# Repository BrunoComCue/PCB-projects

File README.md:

# PCB-projects

Examples of PCB designs made from scratch in order to learn and practice

KiCAD, EAGLE, Altium Designer

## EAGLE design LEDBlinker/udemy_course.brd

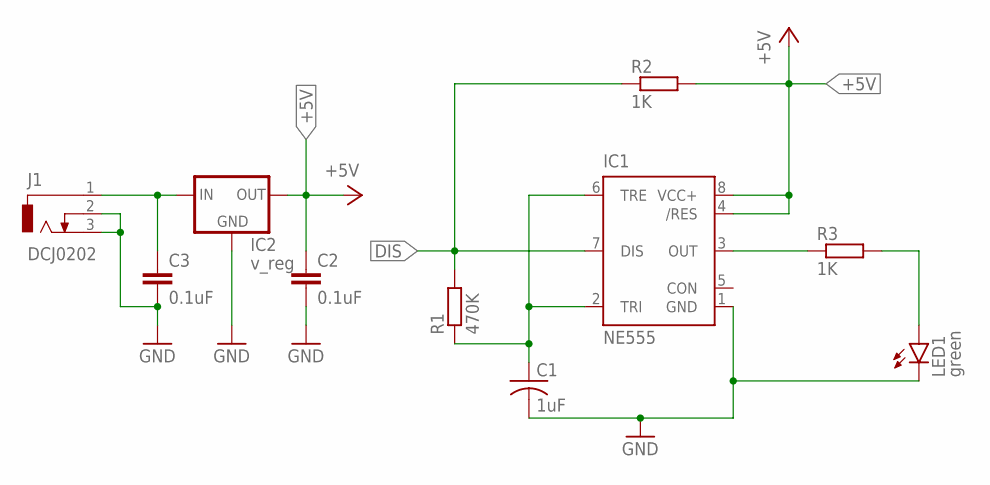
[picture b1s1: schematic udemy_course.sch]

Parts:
C1: 1uF; C050-045X075
C2, C3: 0.1uF; C025-050X050
IC1: NE555; DIL-08
IC2: v_reg; 78XXS
J1: DCJ0202
LED1: green; LED5MM
R1: 470K; 0411/15
R2, R3: 1K; 0411/15

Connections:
+5V: C2.1, IC1.4 (/RES), IC1.8 (VCC+), IC2.OUT, R2.2
DIS: IC1.7 (DIS), R1.2, R2.1
GND: C1.2, C2.2, C3.2, IC1.1 (GND), IC2.GND, J1.2, J1.3, LED1.K (C)
unnamed: C3.1, IC2.IN, J1.1
unnamed: IC1.3 (OUT), R3.1
unnamed: LED1.A, R3.2
unnamed: C1.1, IC1.2 (TRI), IC1.6 (TRE), R1.1

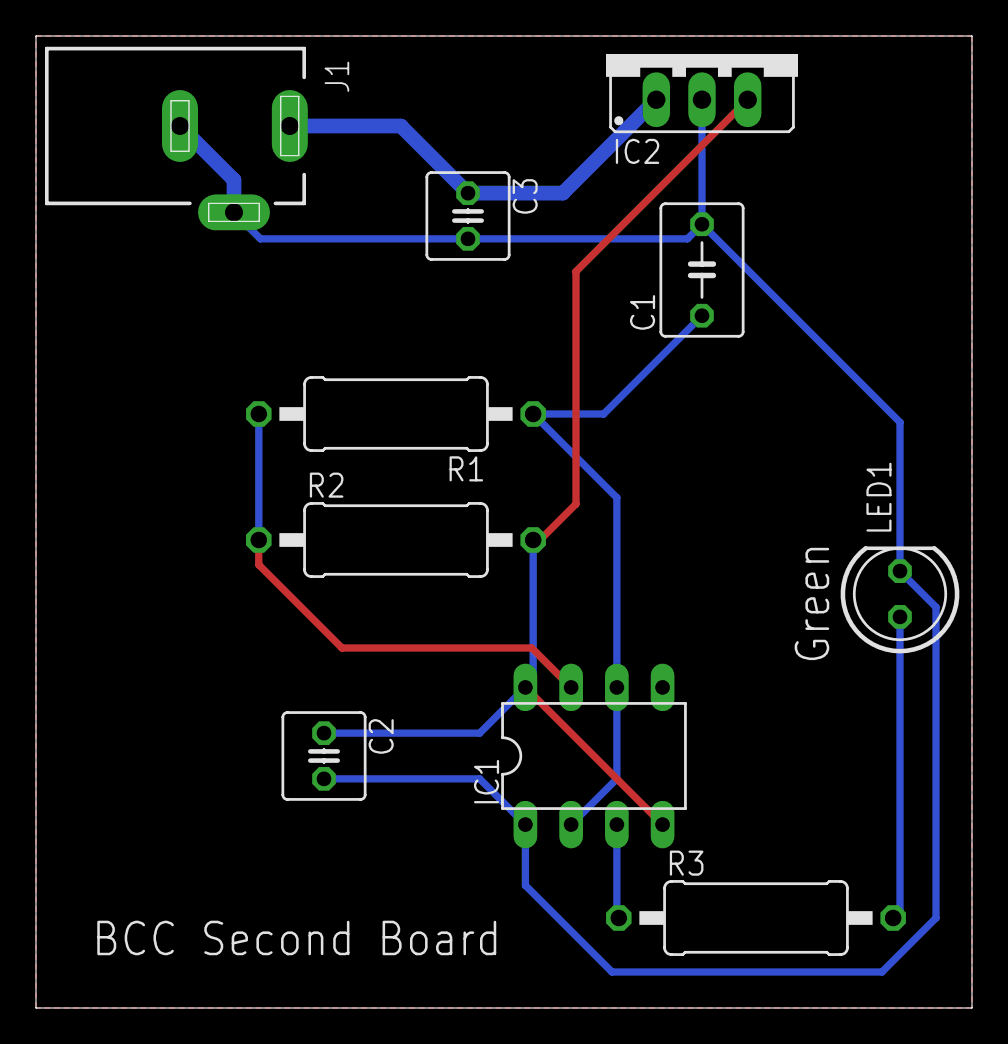
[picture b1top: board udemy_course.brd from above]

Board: 2 copper layers, 52.0 x 54.0 mm, 10 parts (0 on the bottom side), 7 nets.

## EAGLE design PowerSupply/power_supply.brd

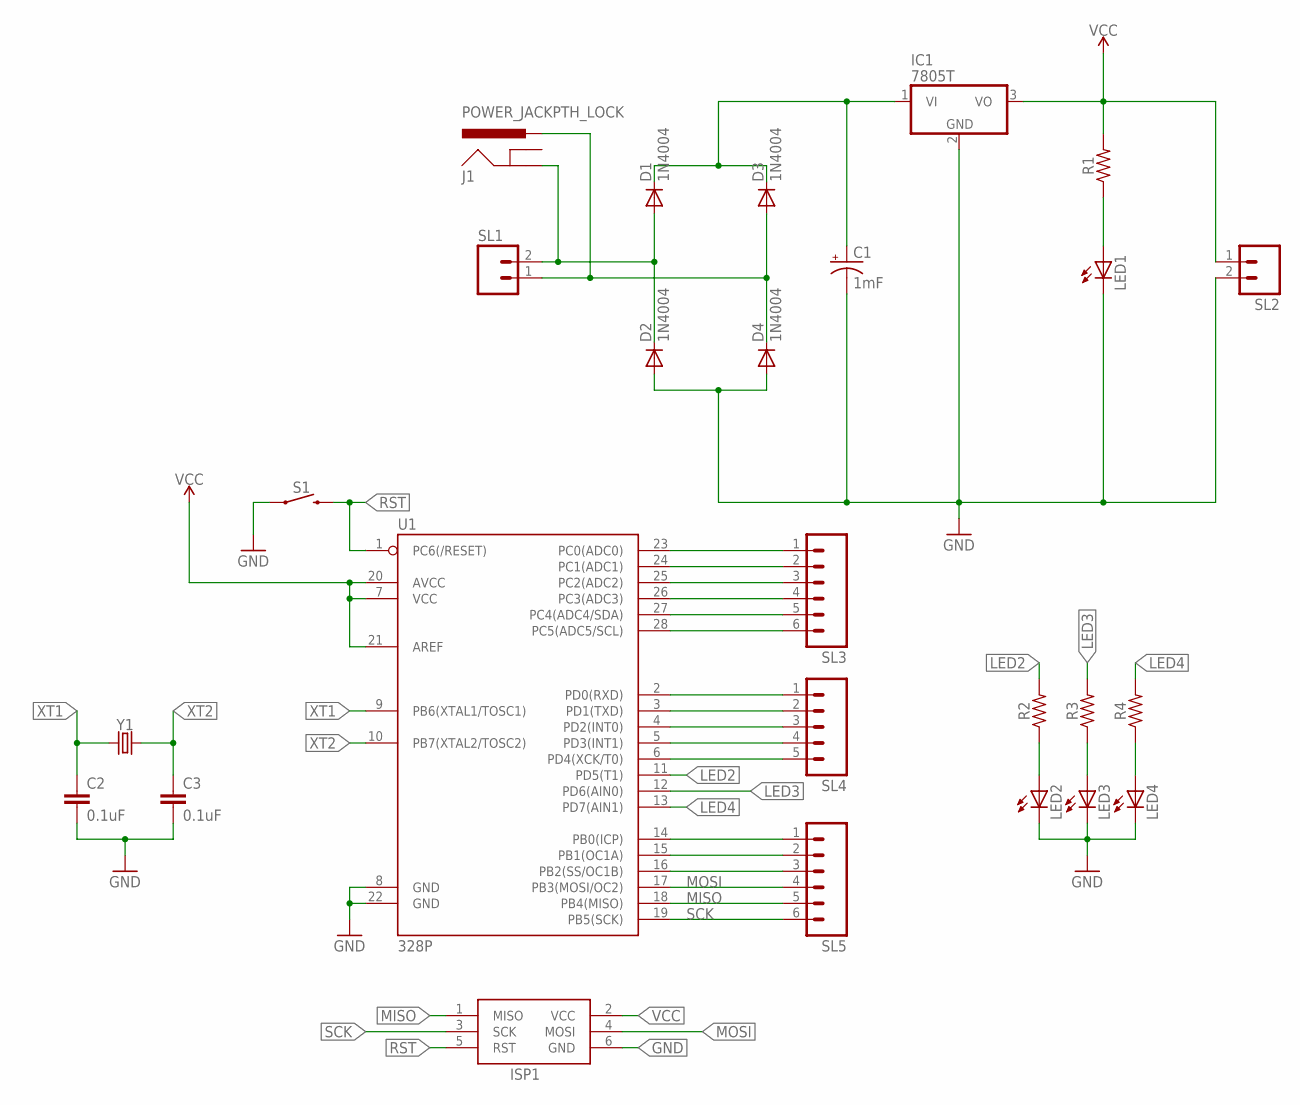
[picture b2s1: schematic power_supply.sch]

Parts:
C1: 1mF; CPOL-RADIAL-5MM-10MM
C2, C3: 0.1uF; CAP-PTH-SMALL-KIT
D1, D2, D3, D4: 1N4004; DO41-10
IC1: 7805T; TO220H
ISP1: AVRISP-6; AVRISP
J1: POWER_JACKPTH_LOCK; POWER_JACK_PTH_LOCK
LED1: LED5MM
LED2, LED3, LED4: LED3MM
R1, R2, R3, R4: AXIAL-0.3
S1: MOMENTARY-SWITCH-SPST-PTH-6.0MM; TACTILE_SWITCH_PTH_6.0MM
SL1, SL2: M02; 02P
SL3, SL5: M06; 06P
SL4: M05; 05P
U1: 328P; DIP28
Y1: CRYSTALPTH-HC49US; HC49US

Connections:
GND: C1.-, C2.2, C3.2, D2.A, D4.A, IC1.2 (GND), ISP1.6 (GND), LED1.K (C), LED2.K (C), LED3.K (C), LED4.K (C), S1.1, SL2.2, U1.8 (GND), U1.22 (GND)
LED2: R2.P$2 (2), U1.11 (PD5(T1))
LED3: R3.P$2 (2), U1.12 (PD6(AIN0))
LED4: R4.P$2 (2), U1.13 (PD7(AIN1))
MISO: ISP1.1 (MISO), SL5.5, U1.18 (PB4(MISO))
MOSI: ISP1.4 (MOSI), SL5.4, U1.17 (PB3(MOSI/OC2))
unnamed: D1.A, D2.C, J1.GND, SL1.2
unnamed: D3.A, D4.C, J1.PWR, SL1.1
unnamed: C1.+, D1.C, D3.C, IC1.1 (VI)
unnamed: SL3.1, U1.23 (PC0(ADC0))
unnamed: LED1.A, R1.P$1 (1)
unnamed: LED2.A, R2.P$1 (1)
unnamed: LED3.A, R3.P$1 (1)
unnamed: LED4.A, R4.P$1 (1)
unnamed: SL3.2, U1.24 (PC1(ADC1))
unnamed: SL3.3, U1.25 (PC2(ADC2))
unnamed: SL3.4, U1.26 (PC3(ADC3))
unnamed: SL3.5, U1.27 (PC4(ADC4/SDA))
unnamed: SL3.6, U1.28 (PC5(ADC5/SCL))
unnamed: SL4.5, U1.6 (PD4(XCK/T0))
unnamed: SL4.4, U1.5 (PD3(INT1))
unnamed: SL4.3, U1.4 (PD2(INT0))
unnamed: SL4.2, U1.3 (PD1(TXD))
unnamed: SL4.1, U1.2 (PD0(RXD))
unnamed: SL5.1, U1.14 (PB0(ICP))
unnamed: SL5.2, U1.15 (PB1(OC1A))
unnamed: SL5.3, U1.16 (PB2(SS/OC1B))
RST: ISP1.5 (RST), S1.3 (2), U1.1 (PC6(/RESET))
SCK: ISP1.3 (SCK), SL5.6, U1.19 (PB5(SCK))
VCC: IC1.3 (VO), ISP1.2 (VCC), R1.P$2 (2), SL2.1, U1.7 (VCC), U1.20 (AVCC), U1.21 (AREF)
XT1: C2.1, U1.9 (PB6(XTAL1/TOSC1)), Y1.1
XT2: C3.1, U1.10 (PB7(XTAL2/TOSC2)), Y1.2

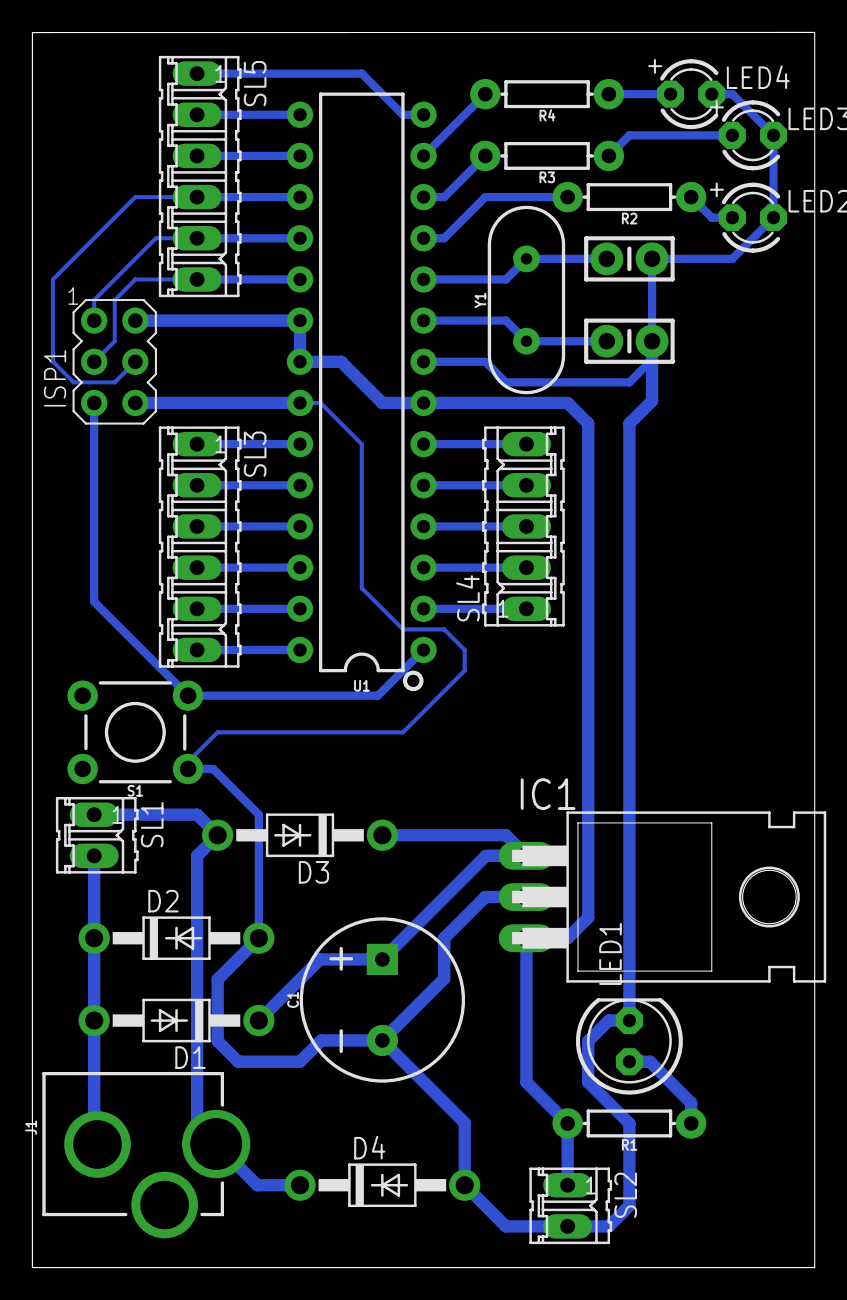
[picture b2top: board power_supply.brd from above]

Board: 2 copper layers, 48.3 x 76.2 mm, 26 parts (0 on the bottom side), 32 nets.

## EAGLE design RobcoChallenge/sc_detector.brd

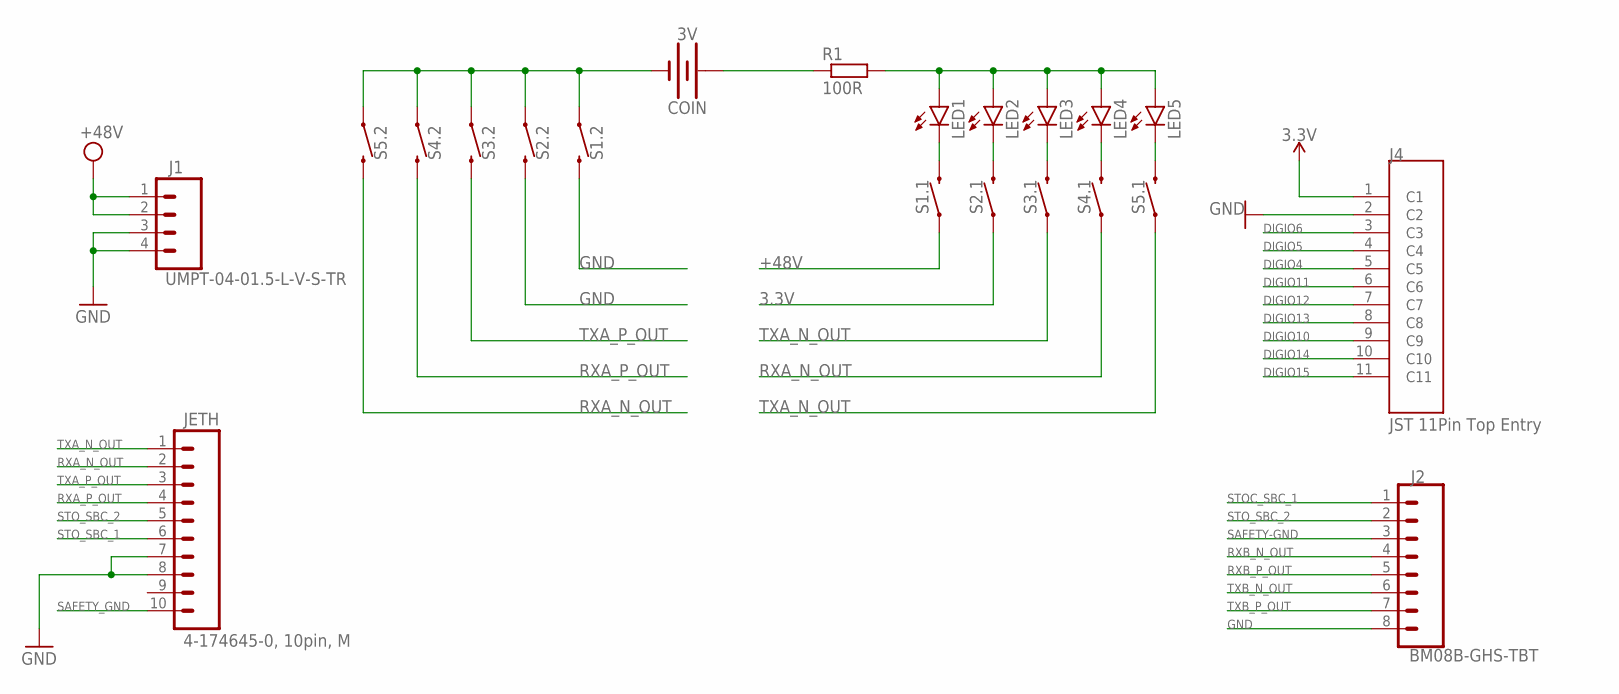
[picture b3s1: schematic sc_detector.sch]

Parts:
COIN: 3V; BATTCON_12MM
J1: UMPT-04-01.5-L-V-S-TR; JST-4-SMD
J2: BM08B-GHS-TBT; 1X08_SMD_MALE
J4: JST 11Pin Top Entry; ROBCO_CONN
JETH: 4-174645-0, 10pin, M; 1X10_SMD_MALE
LED1, LED2, LED3, LED4, LED5: LEDCHIP-LED0805; CHIP-LED0805
R1: 100R; R0805
S1.1, S1.2, S2.1, S2.2, S3.1, S3.2, S4.1, S4.2, S5.1, S5.2: MOMENTARY-SWITCH-SPST-SMD-6.0X3.5MM; TACTILE_SWITCH_SMD_6.0X3.5MM

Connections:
3.3V: J4.1 (C1), S2.1.1
+48V: J1.1, J1.2, S1.1.1
DIGIO4: J4.5 (C5)
DIGIO5: J4.4 (C4)
DIGIO6: J4.3 (C3)
DIGIO10: J4.9 (C9)
DIGIO11: J4.6 (C6)
DIGIO12: J4.7 (C7)
DIGIO13: J4.8 (C8)
DIGIO14: J4.10 (C10)
DIGIO15: J4.11 (C11)
GND: J1.3, J1.4, J2.8, J4.2 (C2), JETH.7, JETH.8, S1.2.2, S2.2.2
IN: LED1.A, LED2.A, LED3.A, LED4.A, LED5.A, R1.2
unnamed: LED5.C, S5.1.2
unnamed: LED3.C, S3.1.2
unnamed: LED1.C, S1.1.2
unnamed: LED2.C, S2.1.2
unnamed: LED4.C, S4.1.2
unnamed: COIN.PWR@1 (+), R1.1
NEG: COIN.GND (-), S1.2.1, S2.2.1, S3.2.1, S4.2.1, S5.2.1
RXA_N_OUT: JETH.2, S4.1.1, S5.2.2
RXA_P_OUT: JETH.4, S4.2.2
RXB_N_OUT: J2.4
RXB_P_OUT: J2.5
SAFETY-GND: J2.3
SAFETY_GND: JETH.10
STOC_SBC_1: J2.1
STO_SBC_1: JETH.6
STO_SBC_2: J2.2, JETH.5
TXA_N_OUT: JETH.1, S3.1.1, S5.1.1
TXA_P_OUT: JETH.3, S3.2.2
TXB_N_OUT: J2.6
TXB_P_OUT: J2.7

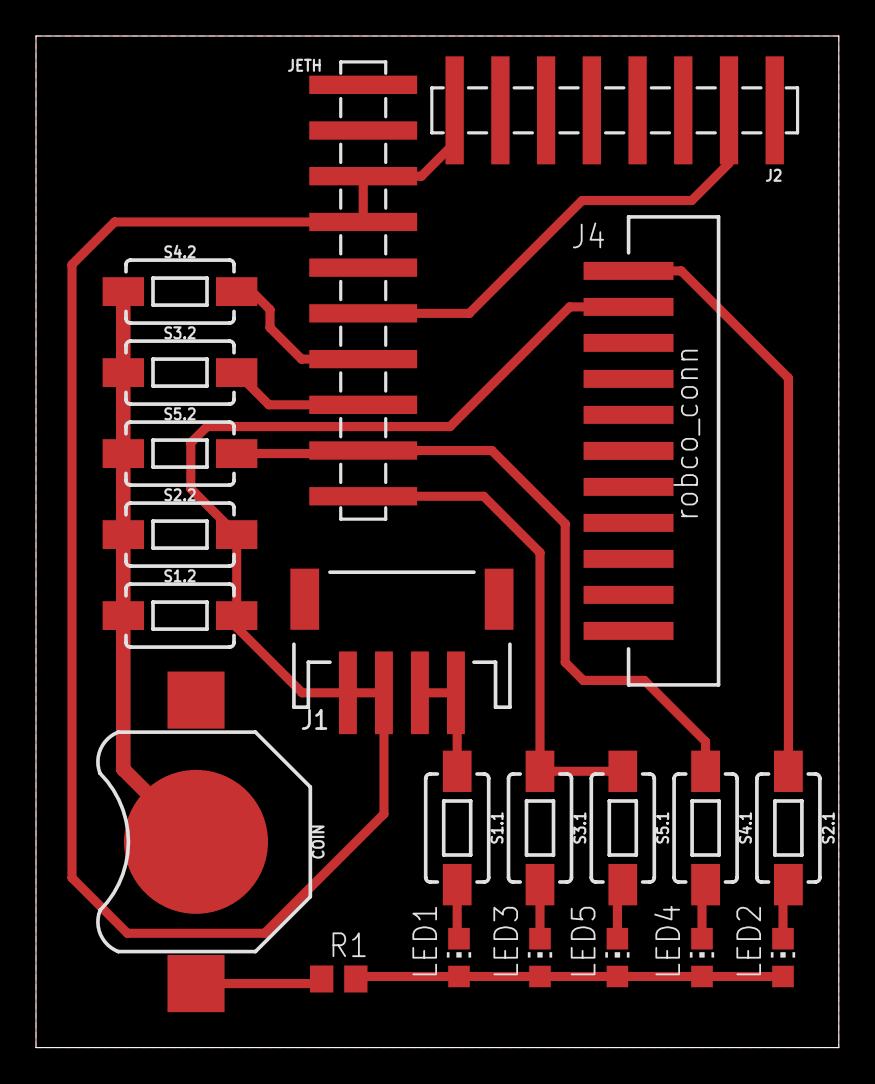
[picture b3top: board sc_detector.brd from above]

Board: 2 copper layers, 44.6 x 56.2 mm, 21 parts (0 on the bottom side), 16 nets.

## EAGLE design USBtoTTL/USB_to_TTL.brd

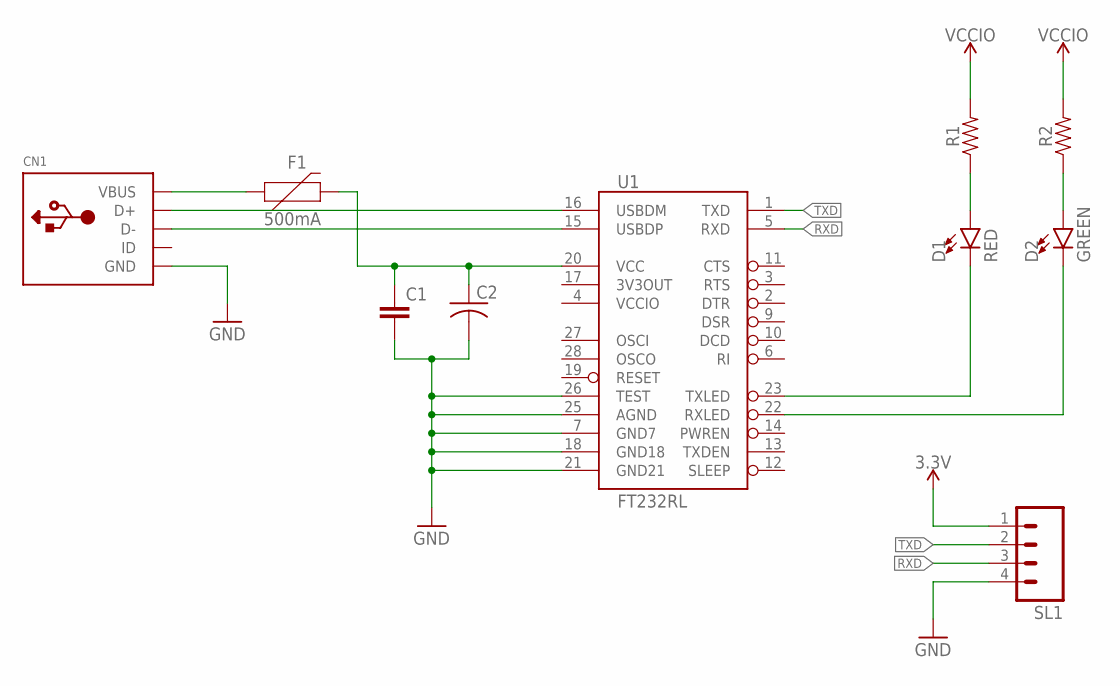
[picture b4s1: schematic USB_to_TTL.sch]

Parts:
C1: C-EUC1206; C1206
C2: C-USC1206; C1206
CN1: USBMINIB; USB-MINIB
D1: RED; LED-1206
D2: GREEN; LED-1206
F1: 500mA; 1206
R1, R2: 1206
SL1: M04; 04P
U1: FT232RL; SSOP28DB

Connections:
3.3V: SL1.1
GND: C1.2, C2.2, CN1.GND, SL1.4, U1.7 (GND7), U1.18 (GND18), U1.21 (GND21), U1.25 (AGND), U1.26 (TEST)
unnamed: CN1.VBUS, F1.1
unnamed: C1.1, C2.1, F1.2, U1.20 (VCC)
unnamed: CN1.D+, U1.16 (USBDM)
unnamed: CN1.D-, U1.15 (USBDP)
unnamed: D1.C, U1.23 (TXLED)
unnamed: D2.C, U1.22 (RXLED)
unnamed: D1.A, R1.1
unnamed: D2.A, R2.1
RXD: SL1.3, U1.5 (RXD)
TXD: SL1.2, U1.1 (TXD)
VCCIO: R1.2, R2.2, U1.4 (VCCIO)

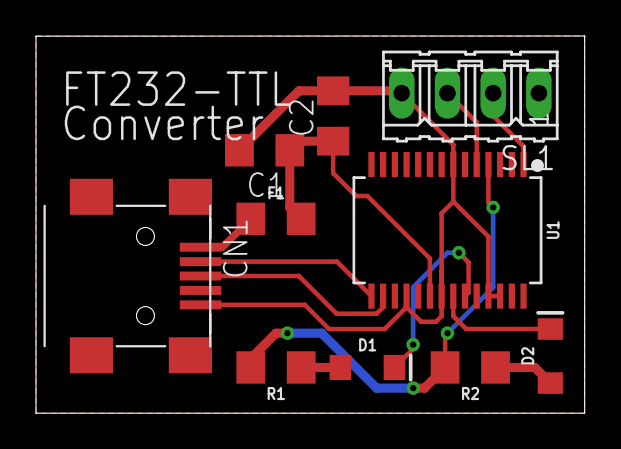
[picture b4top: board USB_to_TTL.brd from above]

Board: 2 copper layers, 30.5 x 21.0 mm, 10 parts (0 on the bottom side), 12 nets.

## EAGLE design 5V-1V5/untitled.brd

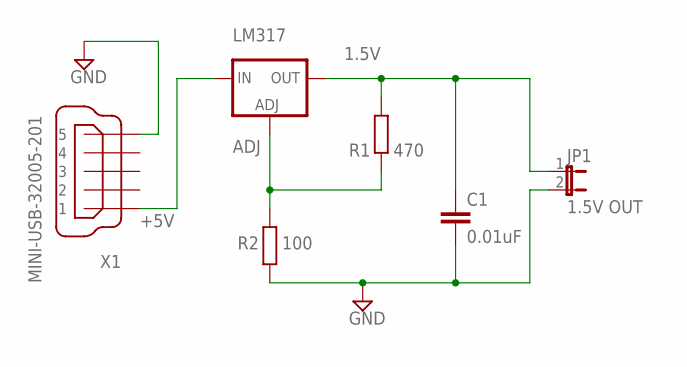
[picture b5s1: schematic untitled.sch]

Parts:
C1: 0.01uF; C050-025X075
JP1: 1.5V OUT; JP1
LM317: LM317TL; 317TL
R1: 470; 0204/7
R2: 100; 0204/7
X1: MINI-USB-32005-201; 32005-201

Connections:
1.5V: C1.1, JP1.1, LM317.2 (OUT), R1.2
+5V: LM317.3 (IN), X1.1
ADJ: LM317.1 (ADJ), R1.1, R2.2
GND: C1.2, JP1.2, R2.1, X1.5

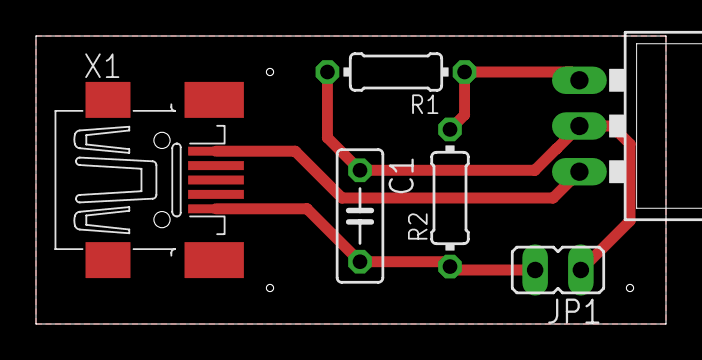
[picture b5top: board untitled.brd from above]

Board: 2 copper layers, 35.0 x 16.0 mm, 6 parts (0 on the bottom side), 4 nets.

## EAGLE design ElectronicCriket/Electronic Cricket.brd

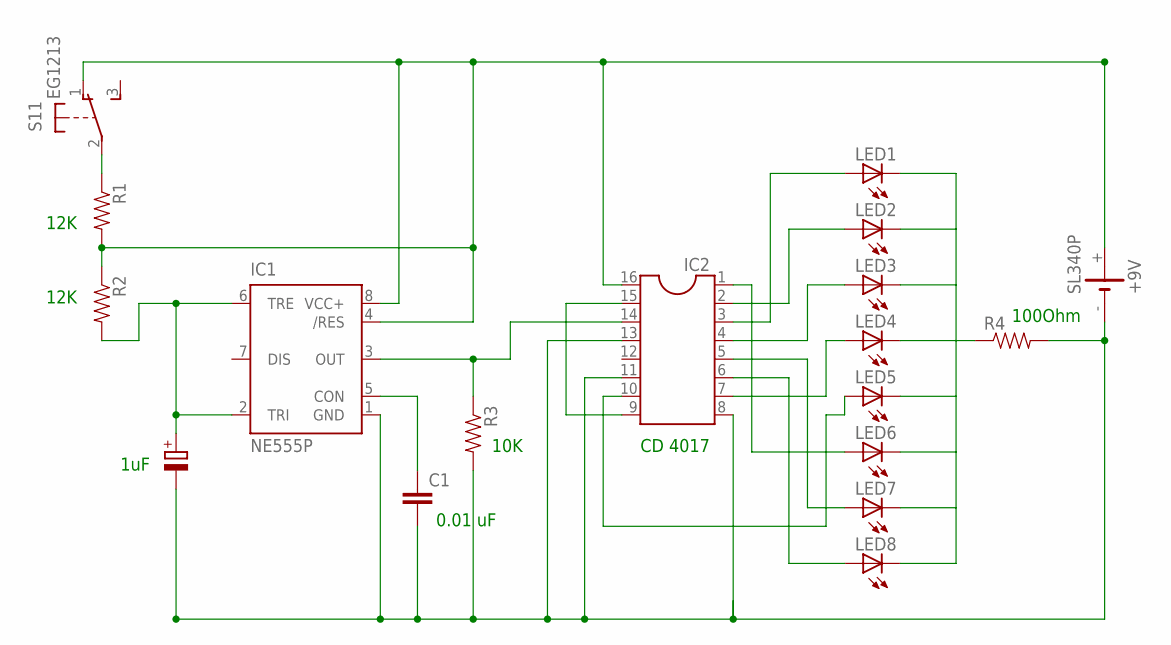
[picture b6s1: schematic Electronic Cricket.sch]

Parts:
+9V: SL340P; SL-340/P3.6V
C1: C2.5/6; C2.5-6
IC1: NE555P; DIL-08
IC2: DIL16
LED1, LED2, LED3, LED4, LED5, LED6, LED7, LED8: LEDB156; Q62902-B156
R1, R2, R3, R4: RESISTORAXIAL-0.3; AXIAL-0.3
S1: EG1213

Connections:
unnamed: IC2.3, LED1.A
unnamed: IC2.2, LED2.A
unnamed: IC2.4, LED3.A
unnamed: IC2.7, LED4.A
unnamed: IC2.10, LED5.A
unnamed: IC2.1, LED6.A
unnamed: IC2.5, LED7.A
unnamed: IC2.9, IC2.15
unnamed: +9V.-, C1.2, IC1.1 (GND), IC2.8, IC2.11, IC2.13, R3.P$2 (2), R4.P$2 (2)
unnamed: IC2.6, LED8.A
unnamed: R1.P$1 (1), S1.2
unnamed: LED1.K (C), LED2.K (C), LED3.K (C), LED4.K (C), LED5.K (C), LED6.K (C), LED7.K (C), LED8.K (C), R4.P$1 (1)
unnamed: IC1.3 (OUT), IC2.14, R3.P$1 (1)
unnamed: +9V.+, IC1.4 (/RES), IC1.8 (VCC+), IC2.16, R1.P$2 (2), R2.P$1 (1), S1.1 (O)
unnamed: IC1.2 (TRI), IC1.6 (TRE), R2.P$2 (2)
unnamed: C1.1, IC1.5 (CON)

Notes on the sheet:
12K
10K
100Ohm
1uF
0.01 uF
CD 4017

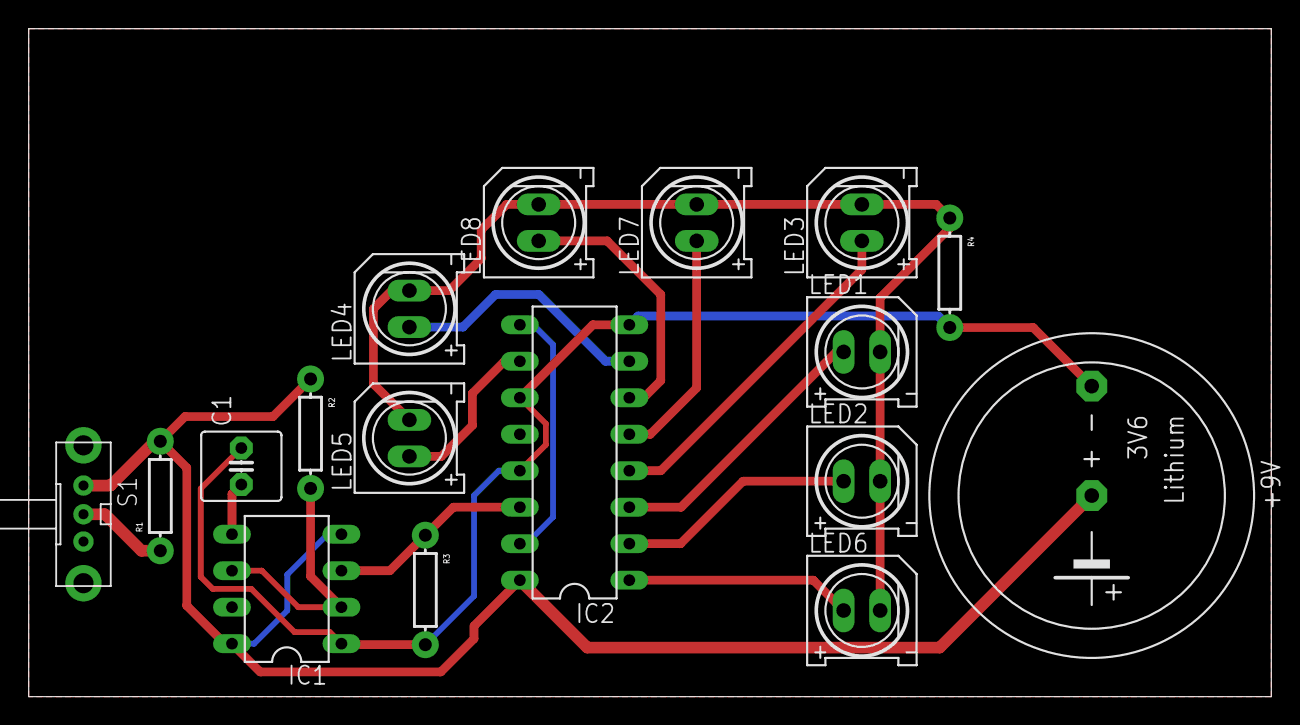
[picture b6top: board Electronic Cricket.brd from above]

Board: 2 copper layers, 86.5 x 46.5 mm, 17 parts (0 on the bottom side), 16 nets.

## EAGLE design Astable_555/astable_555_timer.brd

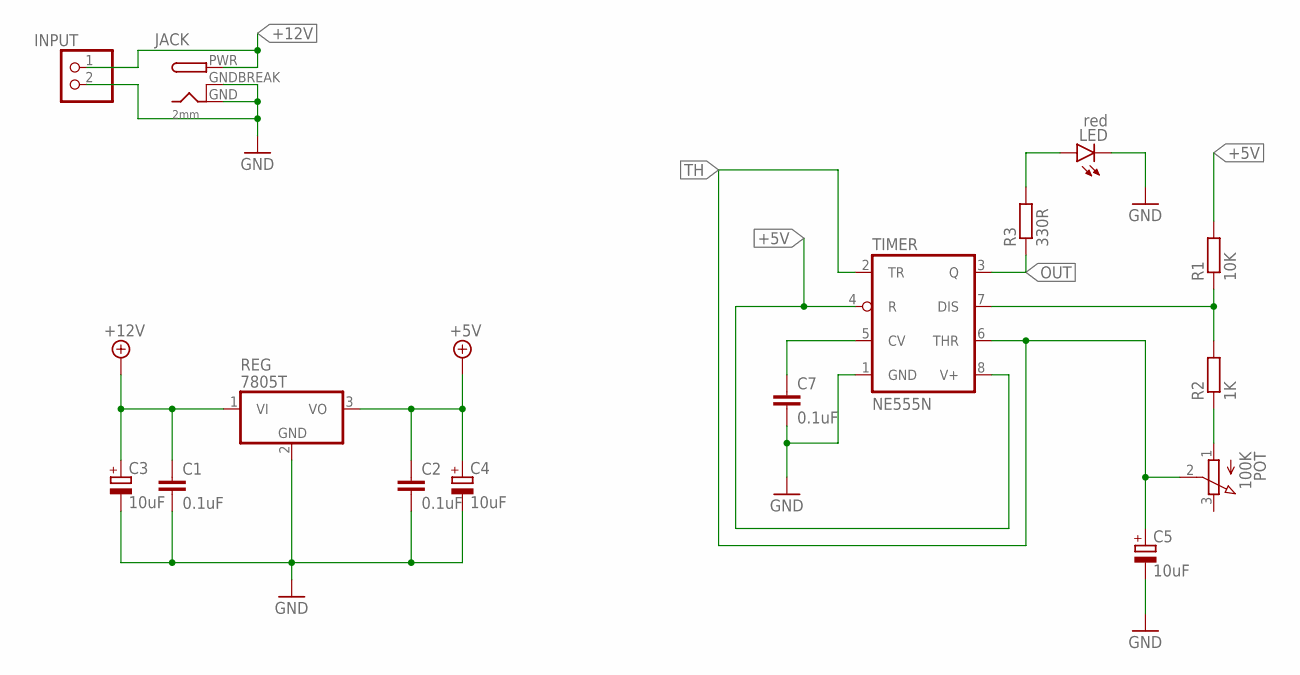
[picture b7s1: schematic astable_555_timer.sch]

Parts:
C1, C2, C7: 0.1uF; C050-030X075
C3, C4, C5: 10uF; E3,5-8
INPUT: PINHD-1X2; 1X02
JACK: 2mm; DCJACK_2MM_PTH
LED: red; LED5MM
POT: 100K; 3RP/1610N
R1: 10K; 0207/10
R2: 1K; 0207/10
R3: 330R; 0207/10
REG: 7805T; TO220H
TIMER: NE555N; DIL08

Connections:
+5V: C2.1, C4.+, R1.2, REG.3 (VO), TIMER.4 (R), TIMER.8 (V+)
+12V: C1.1, C3.+, INPUT.1, JACK.PWR, REG.1 (VI)
GND: C1.2, C2.2, C3.-, C4.-, C5.-, C7.2, INPUT.2, JACK.GND, JACK.GNDBREAK, LED.K (C), REG.2 (GND), TIMER.1 (GND)
unnamed: LED.A, R3.2
unnamed: R1.1, R2.2, TIMER.7 (DIS)
unnamed: POT.1 (A), R2.1
unnamed: C7.1, TIMER.5 (CV)
OUT: R3.1, TIMER.3 (Q)
TH: C5.+, POT.2 (S), TIMER.2 (TR), TIMER.6 (THR)

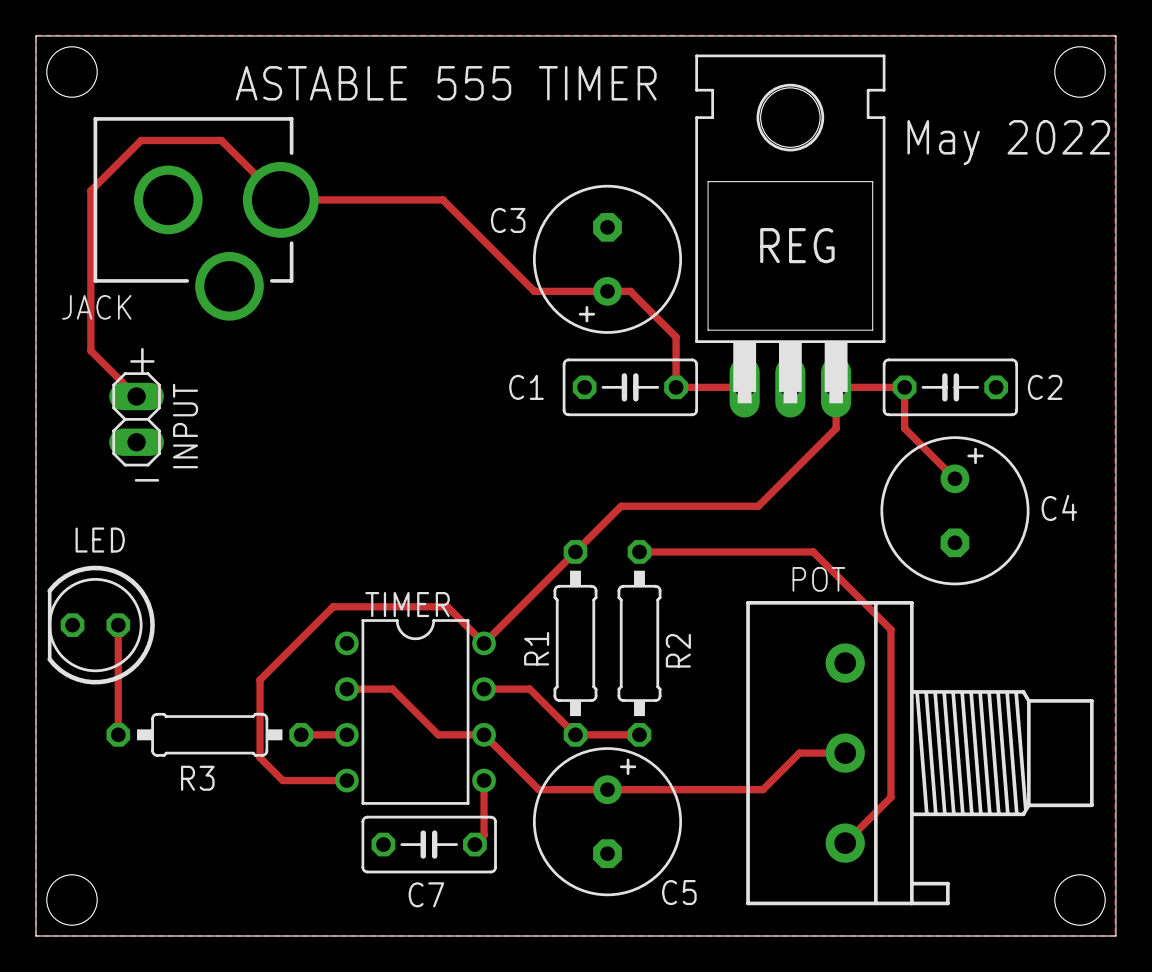
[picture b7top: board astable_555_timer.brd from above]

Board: 2 copper layers, 60.0 x 50.0 mm, 15 parts (0 on the bottom side), 9 nets.

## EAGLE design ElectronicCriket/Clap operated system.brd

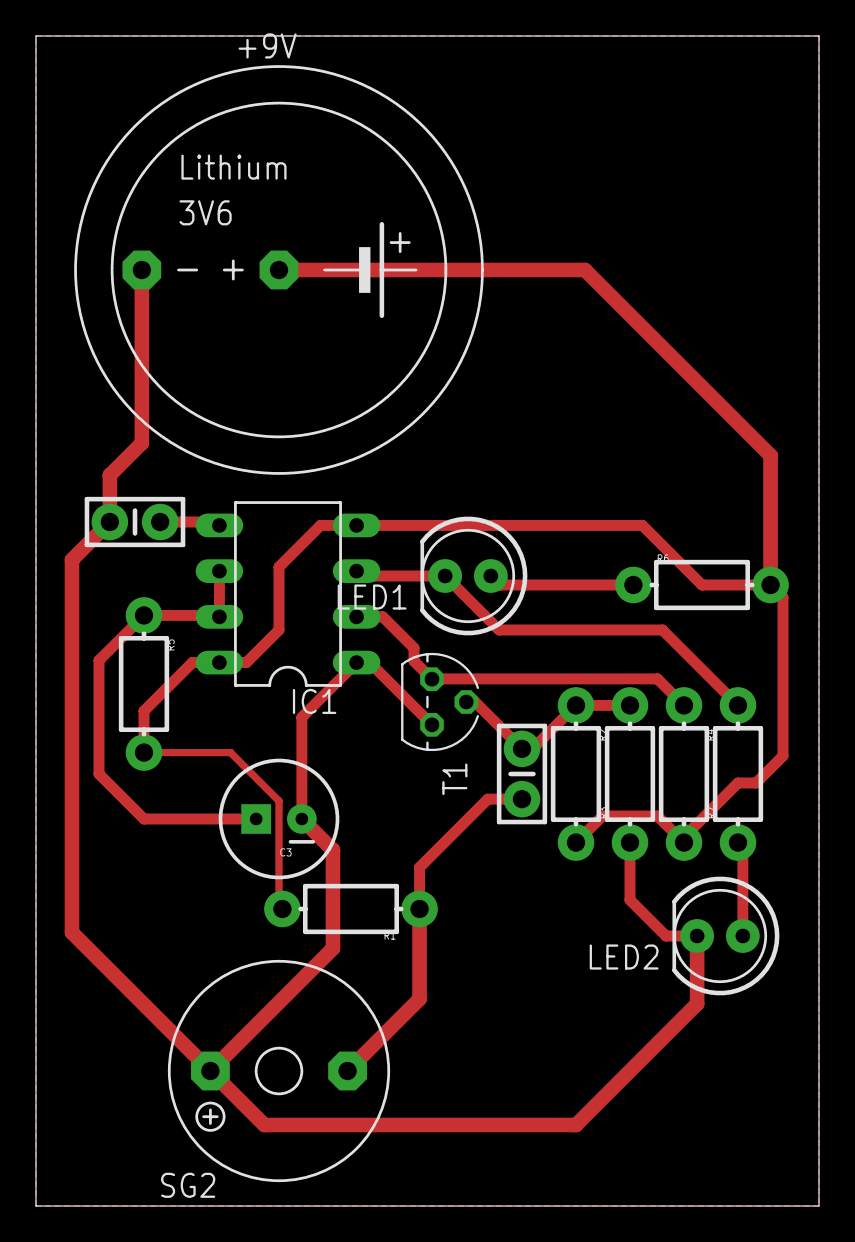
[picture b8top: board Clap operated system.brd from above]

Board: 2 copper layers, 43.5 x 65.0 mm, 16 parts (0 on the bottom side), 10 nets.

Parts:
+9V: SL340P; SL-340/P3.6V
C1, C2: CAP-PTH-SMALL-KIT
C3: CPOL-RADIAL-100UF-25V
IC1: NE555P; DIL-08
LED1, LED2: LED5MM
R1, R2, R3, R4, R5, R6, R7: AXIAL-0.3-KIT
SG2: F/TMB
T1: BC547; TO92

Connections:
unnamed: C1.1, R1.P$1, SG2.-
unnamed: C1.2, R2.P$1, R3.P$2, T1.2
unnamed: IC1.2, R4.P$1, T1.3
unnamed: C3.1, IC1.6, IC1.7, R5.P$1
unnamed: C2.1, IC1.5
unnamed: IC1.3, LED1.K, R7.P$2
unnamed: LED2.A, R7.P$1
unnamed: +9V.+, IC1.4, IC1.8, R1.P$2, R2.P$2, R4.P$2, R5.P$2, R6.P$2
unnamed: LED1.A, R6.P$1
unnamed: +9V.-, C2.2, C3.2, IC1.1, LED2.K, R3.P$1, SG2.+, T1.1

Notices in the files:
parts and their libraries:
SparkFun-Capacitors: Licensing: CC v3.0 Share-Alike You are welcome to use this library for commercial purposes.
SparkFun-Capacitors: Licensing: Creative Commons ShareAlike 4.0 International - https://creativecommons.org/licenses/by-sa/4.0
